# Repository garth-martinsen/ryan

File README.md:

# ryan
python projects collaborating with Ryan Pullen

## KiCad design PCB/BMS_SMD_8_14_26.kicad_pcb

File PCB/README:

This dir is to archive PCB designs and Simulations for the BMS Project.

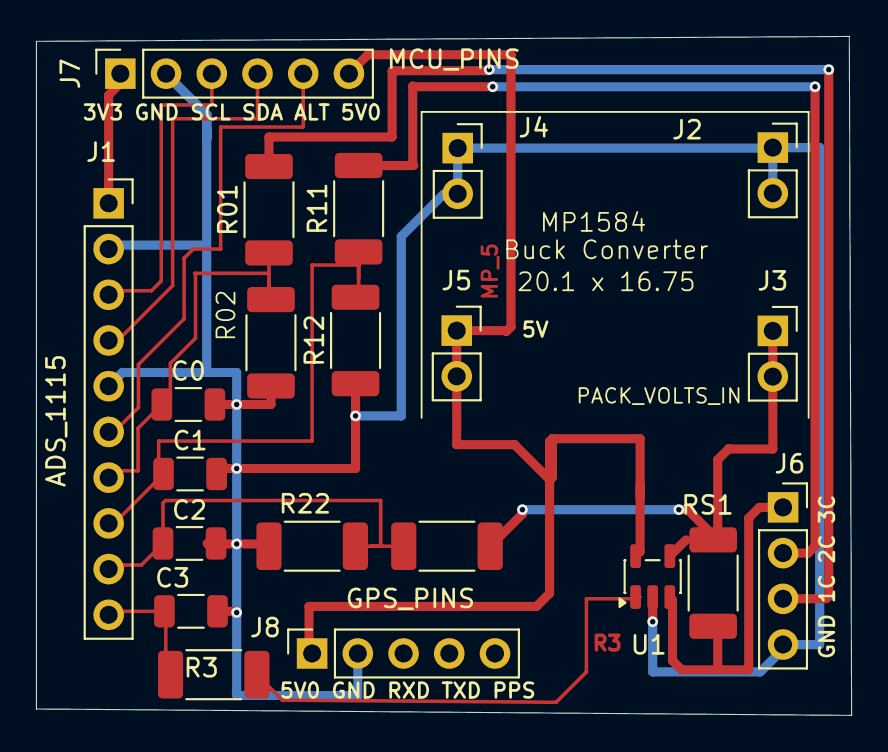
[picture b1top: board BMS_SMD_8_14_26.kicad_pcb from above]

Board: 2 copper layers, 45.3 x 37.7 mm, 21 parts (0 on the bottom side), 15 nets.

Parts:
C0, C1, C2, C3: C_1206_3216Metric
J1: ADS_1115; PinSocket_1x10_P2.54mm_Vertical
J2: MP_OUT-; PinSocket_1x02_P2.54mm_Vertical
J3: MP_OUT+; PinSocket_1x02_P2.54mm_Vertical
J4: MP_VIN-; PinSocket_1x02_P2.54mm_Vertical
J5: MP_VIN+; PinSocket_1x02_P2.54mm_Vertical
J6: VTAP_INPUTS; PinSocket_1x04_P2.54mm_Vertical
J7: MCU_PINS; PinSocket_1x06_P2.54mm_Vertical
J8: GPS_PINS; PinSocket_1x05_P2.54mm_Vertical
R01, R12, R22: 100K; R_2010_5025Metric_Pad1.40x2.65mm_HandSolder
R02, R21: 330K; R_2010_5025Metric_Pad1.40x2.65mm_HandSolder
R3: 1k; R_2010_5025Metric_Pad1.40x2.65mm_HandSolder
R11: 220K; R_2010_5025Metric_Pad1.40x2.65mm_HandSolder
RS1: 0.05Ω; R_2010_5025Metric_Pad1.40x2.65mm_HandSolder
U1: INA180A1; SOT-23-5

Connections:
/3V3: J1.1, J7.1
/ALRT: J1.6, J7.5
/MP_5: J5.1, J5.2, J7.6, J8.1, U1.5 (V+)
/SCL: J1.3, J7.3
/SDA: J1.4, J7.4
A0: C0.1, J1.7, R01.1, R02.2
A1: C1.1, J1.8, R11.1, R12.2
A2: C2.1, J1.9, R21.1, R22.2
A3: C3.1, J1.10, R3.1
C0: J6.3, R01.2
C1: J6.2, R11.2
GND: C0.2, C1.2, C2.2, C3.2, J1.2, J1.5, J2.1, J2.2, J4.1, J4.2, J6.4, J7.2, J8.2, R02.1, R12.1, R22.1, U1.2 (GND)
unnamed: R3.2, U1.1
RS+: J6.1, RS1.1, U1.3 (+)
RS-: J3.1, J3.2, R21.2, RS1.2, U1.4 (-)

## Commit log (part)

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2025-08-10 Initial commit. adc_client and db_server are working. Default mode is calibrate. adc_client requests input on the vin value. This is sent to the server along with the measurement values. There it is 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
2025-08-10 added the rt_db file which sqlite3 opens on .
2025-08-10 DatabaseInterface receives save requests with msg from DataController. DatabaseInterface pops the purpose field and ensures correct type [c|m] is set, gets the local time and creates the insert_str a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
2025-08-10 commented out and modified the if logic on msgs.
2025-08-10 added .gitignore file
2025-08-12 Renamed test_calibrate.py to test_dbi.py. Added assert statements so each test method returns boolean.
2025-08-13 Added 1 to all server response purposes ie: 10-> 11 etc.
2025-08-13 Created a 2nd Client: scheduler_client.py. It will send requests to the server that will be fulfilled by the adc_client. eg: Measure(channel) and Calibrate(channel, vin), getLut(channel) and getKeep(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
2025-08-13 From laptop where it was working.
2025-08-15 added more comments to clarify
2025-08-15 some changes in comments.
2025-08-15 db_server: "client_can_respond" was made a global variable so different threads can see it. Attempted to get one thread (handle_scheduler_client) to send a msg to the adc_client to make a measurement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
2025-08-15 test_dbi.py: Fixed assert statements so the syntax is correct and each has a msg.
2025-08-15 Tested the DataController : constructor, save_measurement, save_calibration, cfg_id, lut_files. I can say that if the dataController is passed a msg from the adc_client with data, that the data is sa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
2025-08-25 Added instructions to clear locked ipaddress. Simplified db_server to ease understanding of code. Used a dict to lookup the response msg for a given purpose in the msg just received. Used global vars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
2025-08-25 Clarified instructions in this learning class.
2025-08-25 No longer hanging. working correctly...
2025-08-26 Small changes in response msgs.
2025-08-28 Added a message if only one client is connected. Server cannot forward to either client if both are not connected. this is important for 100, 200 cmds from gui_client and for 101, 201 responses from 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
2025-08-28 Added class gui_data to hold data from Server and measurements and calibrations from adc_client. Still need to provide the CONFIG records from the CONFIG table. Added debugging lists: rqsts_to_server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
2025-09-03 Changed rsps to responses in dict names and methods. Added lists to capture msgs with purpose > 100 so that they can be sent to the correct client. msgs with purpose:100 from gui_client to adc_client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
2025-09-06 removed some comments.
2025-09-06 Added CONFIG_NOLUTS = namedtuple, Added id to the BMS namedtuple,
2025-09-06 Changed to use AI advice: added three global vars: adc_conn, gui_conn, sender_id. Removed two dicts: sockets_by_addr, client_names_by_addr , Added sender_id property to every msg.Gave each of adc_con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
2025-09-06 test_dc.py is working as far as is defined,.
2025-09-26 the *.schema files were added for the only two tables in dir data. The rt_db is a binary file and will be removed from git. The rt_db can be created by entering sqlite3 rt_db. The tables CONFIG and B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
2025-09-27 Removed a lot of code from adc_client.py and handled it in adc_data_controller.py
2025-09-27 Moved complexity to gui_data_controller.py. The gui_client.py now deals only with connect, send, receive msgs. The msgs it sends will be created in the gui_data_controller, which also configures and 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
2025-09-27 Correct the import in db_server.py for svr_data_controller. The new class: SvrDataController, is called from db_server with a msg which it checks for rqrd fields, then extracts those field: purpose ,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
2025-09-27 Added two new fields to db table CONFIG: ADC_GAIN, and ADC_SAMPLE_RATE
2025-10-06 Changed dbpath in data_controller_config.py .
2025-10-18 Modified the ads1x15.py to skip first four conversions because they were usually low. ~line 87,88
2025-10-21 instantiated new class: adc_scheduler as self.adc_scheduler to allow svr_data_controller to schedule_ measurements with wait_time, and repetitions. 2 Added instance variables lsb0 (FS=6.144V) and lsb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
2025-11-03 working to get configs and luts into adc
2025-11-03 Removed method datetimestamp() and replaced it with method timestamp(). The latter is based on time.localtime and not RTC as the former was. This is consistant with the other classes: they all use ti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
2025-11-05 Printed out db_path and cfg_ids to ensure correctness
2025-11-05 Removed commented out parts.
2025-11-05 Modified purpose numbers iaw Message Map. Added method user_requests to allow user to request 100 or 200. Not yet working correctly, but records are saved to db BMS table (wahoo!) . Problems: first r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
2025-11-05 Added initialize gain to 0 (FSR: 6.144V).
2025-11-05 imported scheduler and added instance var: scheduler. constructor has cfg_ids and sockets dict from async_db_server . scheduler instance has sockets and self.Replaced method missing_rqd_fields(...) w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
2025-11-05 removed conn from __init__ and instance variable
2025-12-14 shortened all channel fields to chan and all description fields to use desc. Added field LUT_TS to CONFIG schema to allow timestamp for updates to LUTs, without affecting the other fields of the CONF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
2025-12-16 Added LUT_INFO namedtuple to allow updating LUT. Changed namedtuple name from Short_Record to Abbrev. Prefixed all internal methods with underscore eg: _format_insert(...). Added self.cx.commit() aft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
2025-12-16 Have 9 test methods. All passing.
2025-12-16 changes for test_adc.py
2025-12-18 Created calculated luts for testing.
2025-12-19 Created class LutConvert with two methods: odict_to_list(odict: OrderedDict) which returns a List[List[float,float]]. and list_to_odict(jsonlist) which returns an OrderedDict. Using these two methods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
2026-02-22 Removed duplicate call to extract reps.
2026-02-25 gui_client now accesses two servers: adc_ws_server and db_ws_server. To see this work. create three terminal windows, each of which uses virtual environment so they can see module websockets. In the 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
2026-02-25 Adding the database_interface and its config file
2026-02-25 Tool to load records into the tables in sqlite3 rt_db.
2026-03-11 Can be used to populate LUTS table. Also demonstrates lookup_col_vm(0,vm) etc.
2026-03-11 Fixed boundary rules: if vm == lowest key or vm == highest key, return lut{vm], else if vm < lowest Key or vm > highest key, return error statement, else: bracket vm with keys and interpolate to get 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
2026-03-12 Removed mosfet and mosfet_type from namedtuple("Config")...Added purposes dict to give db_cmds meanings.
2026-03-22 Changed bms schema: added FSR, LSB, removed gate_time, store_time, sample_period. Changed Config schema: Added column VD_FRACT.
2026-03-22 Tested with new schemas and fields to be saved to bms table. Tests pass.
2026-03-22 updated to make test_dbi.py to work.
2026-03-23 Moving database to its own dir under ryan.
2026-03-23 Moved the database and schemas to ryan/sqliteDB dir. Now it can be used for any branch of code under ryan eg: simplewebsockets, clientserver, etc.
2026-03-23 added minor changes to lut limit test...
2026-03-26 changed instantiation of DBI to use app_id in liew of (1,2,3) cfg_ids.
2026-04-22 Dropped columns FSR, LSB from BMS table, Added columns: ADC_FSR, ADC_STEPS, ADC_SAMPLE_RATE to table CONFIG. Added line on top of all_schemas.sch: Updated on: a Date.
2026-04-22 Cleaned up LUT process... Started method to populate new table with changed schema. Needs work to finish and test it.
2026-04-25 Added file phoney_gen.py to generate json-worthy messages from adc and gui to dbs. All values are generated. Content of real msgs will be actual measurements.This will be useful in building the messa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
2026-04-29 minor changes for readability
2026-05-06 Removed code to connect to adc_server, leaving only db_server connection code.
2026-05-06 removed reference to adc_server.
2026-05-06 Changed to get all config records in the same rqst/rspns.
2026-05-06 Added TODOs and cleaned up.
2026-05-13 Now can create a=ADC(file) or a=ADC(db). Using the former, I can save a measurement to device file: /data/adc_storage. for analysis. example Command is: a.send_results(a.measure(5004, 2, 12.47, 200))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
2026-05-19 updated the vd_fracts to agree with the resistors in latest PCB.
2026-06-07 updated the BMS and Config namedtuples to agree with the db schemas.
2026-06-07 Added the msgid and other fields and methods to synchronize them with db table schemas and insert strings and namedtuples.
2026-06-07 fixed errors due to uppercase in BMS and Config namedtuples. All Tests pass but some are too db dependent. Fix this later.
2026-06-07 Removed schema_03222026.txt as it was confusing. all_schemas.sch replaces it.
2026-06-08 updated schemas and data
2026-06-14 Split A2D samples into its own table, A2D. It must match its bms_id to bms.id. 3 Changed column name of version_id to version in Config table and modified 4 Four tables now: [CONFIG, BMS, LUTS, A2D]
2026-06-14 The namedtuple BMS no longer has "samples" as its last field. samples will be requested using dbi.get_a2d_samples(bms_id). This should be rare, only when user wants to analyze the samples due to larg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
2026-06-21 working modules for bms_apps. Will provide basis for chatgpt questions and comments.
2026-06-21 simplified the cmd (code) list for gui README file. updated the .gitignore file
2026-06-21 working on tracking down ADC_client disconnection issues. The bms_asyncio_server.clients dict does not refresh the writers when one closes.
2026-06-22 Created a usage doc to help someone know how to run the 3 async apps which communicate with each other.
2026-06-23 added more files to ignore
2026-06-23 in gui/gui_asyncio_client.py: added a funct_desc dict to gui_client can prompt user to input correct msg elements.Function: show_dbi_functions lists t hem. Added input prompts depending on the code(c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
2026-06-23 in svr/bms_asyncio_server.py: Added a tab in printout: Server Received MSG: type: {type(data)} , data: {data} ") to make it stand out in log.
    in svr/database_interface.py: imported funct_desc dict from database_interface_config, added method: create_function_dict() to create a dictionary of codes to call methods, added new function: call_f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
2026-06-23 changed the DTS field value to be time.time(). Who needs ns when localtime has a fractional part?
2026-06-23 database_interface.py: Added function get_cursor(self). It is called in every function that needs dbi connection. Added function get_lut_item(chan, vin) which returns a lut_item containing all LUTS f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
2026-06-23 Moved requirements.txt from svr to bms_async_apps project dir.
2026-06-24 all_schemas.sch: Added new table MSGID to furnish next_msgid.
2026-06-24 added method: get_cursor() so that every call that needs access to the db tables does not repeat the same code.
2026-06-24 removed extraneous commented out lines of code.
2026-06-24 cleaned up
2026-06-28 adc_asyncio_client.py: implemented the adc client response to various commands from GUI. Added a line to ignore non-dict msgs.Roughed in the call to get rtc_time from svr. Needs work and testing. add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
2026-06-28 bms_asyncio_server.py: Cleaned up the Svr response to the client hello msg. database_interface.py: added cmd 302 which calls svr to send time.time() to the esp to set the real time clock (rtc). Revis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
2026-06-28 Old code. No longer used.So small changes.
